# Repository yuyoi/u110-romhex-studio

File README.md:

# U110 RomHex Studio  (WIP)

<p align="center"></p>

Make your own **PCM sample cards for the Roland U-110** (and the other machines that read SN-U110 cards:
U-20, U-220, D-70, CM-32P, CM-64, MV-30, Rhodes 660/760). This is a free, open replacement for the custom-card
tools that never shipped.

> **Made by JunkSmithWizard (JSW) together with Claude (Anthropic's AI).** Claude wrote the code and did the format analysis
> (descrambling, sample coding, tables). JSW built the hardware, burned and tested every card on a real U-110,
> tested cards on a D-70 and a Rhodes 660, and made the debugging calls that cracked it: the known-good D-70 ROM control, the CD4069 noise fix, and
> pointing the D-70 debugging at its card check, which turned up the `SN-U110-` name rule.
> Reverse-engineered and shipped in one day.

Drop in WAV files, set root notes, key ranges and loops, press **Build**. You get a 512 KB image to burn on a
flash chip (e.g. SST39SF040) sitting in a card-slot adapter. Tested on a real U-110: custom multisampled,
looping and one-shot tones play correctly. Also tested on a real D-70 and a real Rhodes 660.

> **D-70 users:** the D-70 only accepts a card whose name starts with `SN-U110-`. The app always writes that
> prefix, so you pick the last 8 characters. Cards built with older versions of the app (any name) work on the
> U-110 but are not seen by the D-70. Rebuild them.

## Demo

**[Listen: u110_demo.mp3](docs/demo/u110_demo.mp3)** (1:42, recorded from a real U-110 playing a custom card)

> **⚠ AUDIO WARNING: turn your volume down first.** This demo has loud, harsh, glitchy digital sounds.

- **0:00: three samples:** custom multisampled tones from a card built with this tool.
- **Then: wavetable:** single-cycle waves and scan-morph tones (Tone → Wavetable). The stepped scan plus the
  U-110's 8-bit delta coding gives a tunable, glitchy "pleasant malfunction" sound.

## Burn cards with an ESP32

Don't have a chip programmer? An **ESP32-S3** can write the card chip itself, over USB or from a web page, for a
few dollars in parts: **[esp32-maskrom-programmer](https://github.com/yuyoi/esp32-maskrom-programmer)** (a working prototype). It wrote
a full 512 KB card image with 0 wrong bytes, no level shifters or resistors on the breadboard.

In the app: **File → Build and Burn to Programmer** (Ctrl+Shift+B) builds the card and sends it straight to the
programmer over USB; **File → Send .bin to Programmer...** sends any 512 KB image. Take the chip out of the synth first, and unplug it from the programmer before you put it back in the synth.

**Built a card, or the ESP32 programmer?** It has only been tested on one bench so far. Please
[open an issue](https://github.com/yuyoi/u110-romhex-studio/issues) and tell us what worked and what didn't
(which synth, which chip, a photo of your setup).

## Screenshots

*Styled after the U-110's front panel: backlit LCD, memory LEDs, a waveform editor with start/loop/end markers,
and colour-coded key zones on the keyboard. Click a key to hear it exactly as the U-110 will play it.*

*The card-slot adapter used for testing: slot header to SST39SF040, with a CD4069 inverting the active-high card
select. Slot pin 34 (SENS, card detect) is tied high to +5 V.*

*Optional (bottom right in the schematic): if you still hear occasional clicks or glitches, a small capacitor on
the inverter helped on the author's adapter (22 pF from CD4069 pin 2, the output of the gate that inverts the card
select, to GND). Your adapter may differ. Details and untested ideas (value, placement, two caps, type) are in
[docs/HARDWARE.md](docs/HARDWARE.md#glitches-decouple-the-logic).*

> **Warning:** if you program the chip with the ESP32 programmer, **disconnect the chip from the programmer (unplug it from the breadboard / ESP wiring) before you put it in the card slot.** An ESP left wired to the address and data lines loads and clamps the synth's 5 V bus, adds noise, and can back-power the board. Simplest: **lift the ESP off the breadboard so it has no connection at all.** Burn with the chip out of the synth; play with it out of the programmer.

## Quick start (Windows)

1. Download **`U110RomHexStudio.exe`** from the [latest release](https://github.com/yuyoi/u110-romhex-studio/releases/latest)
   and run it (check it against `SHA256SUMS.txt` if you like). No install is needed. The exe is unsigned, so Windows may show "Windows
   protected your PC": click **More info > Run anyway**. It takes a few seconds to start.
   Or, from source: install Python 3.10+, run `pip install -r src/requirements.txt`, then `run_from_source.bat`.
2. **File > Open Project** and pick `examples/demo.u110proj` to see a finished card, or start fresh:
   - **+ Tone**, then **Add WAVs**. Several files at once become either one multisampled tone (key zones) or
     one tone per file (drums, FX).
   - Root notes are read from file names (`Piano_C3.wav`, `F#2`, `60`) or from the WAV's own sampler chunk.
     Loop points saved in the WAV (Wavosaur, Audacity, Awave, ...) are used.
   - Waveform: drag **S** (start), **L** (loop start), **E** (end). Wheel zooms, Shift+wheel pans.
     **Auto loop** finds a loop and crossfades it.
   - Click the on-screen keyboard to hear a key **exactly as the U-110 will play it**: the real 8-bit
     encoding, playback rate and loop behaviour.
3. **Build Card...** writes `NAME_BURN.bin` plus a report. Burn it as-is (no byte swap).
4. On the U-110, go to EDIT > PATCH > PART > BAS and change the tone group from `I` to the slot holding the
   card. Insert and remove cards with the power off.

## Character modes (per tone)

| Mode | Sound | Memory |
|---|---|---|
| **STUDIO** | clean, filtered resample | 100% |
| **CRYSTAL** | look-ahead encoder, slightly cleaner, slower build | 100% |
| **DUSTBOX** | SP-style lo-fi: ~26 kHz, no anti-alias filter, drive | ~88% |
| **8-BIT** | early 8-bit sampler: 256 steps, 22-16 kHz, no filter | ~70% |
| **CHIPTUNE** | retro game: 6-4 bit, 16-8 kHz, sample & hold | ~50% or less |

**Amount** sets drive, rate or crush. Playback is always 12-bit, because that's what the U-110's sound chip outputs.

## Limits (set by the card format)

| | |
|---|---|
| Card size | 512 KB, about 496 KB for audio (~15 s at the native 32 kHz) |
| Card name | `SN-U110-` + 8 characters of your choice (the D-70 needs the prefix) |
| Tones | 128 per card |
| Key zones | 12 per tone |
| One sample | max 64 KB: 2 s at 32 kHz. Longer samples are automatically stored at a lower rate and stay in tune |
| Resolution | 12-bit, stored as 8-bit companded DPCM (Roland's "RS-PCM") |

When a card is too full, **Sample rate: Auto** lowers the whole card in semitone steps until it fits.
The memory bar shows how much is used.

## Also in the box

- **File > Import card .bin**: open any SN-U110 card image (a Roland dump or one of your own) to edit it,
  and extract its samples as WAVs.
- **File > Import sampler CD (Akai / Roland S-7xx)**: browse an Akai S1000/S1100 or Roland S-760/S-770 sampler CD (`.iso`,
  `.img`, `.tao`, `.nrg` of the raw disc), pick programs or patches, and they become tones: key ranges, root notes, tuning and loops are kept, stereo L/R pairs
  are mixed to mono, and the samples are trimmed to fit the card (your own tones are never touched). See `docs/AKAI.md`
  and `docs/ROLAND.md`.
- `src/u110card.py` on the command line: `info`, `wavs` (extract samples) and `convert` (MAME card dump to
  burnable connector order).
- `docs/FORMAT.md`: the reverse-engineered card format.
- `docs/HARDWARE.md` + `docs/adapter_schematic.png`: card-slot pinout, adapter wiring and the byte-order pitfall.

## Important: byte order

Images from MAME's `sn-u110-xx.bin` set have address lines **A8..A15 reversed** compared with the card slot.
Burned as-is on a straight-wired adapter, they load with garbled names and no sound. This app always writes
**connector order**, the right order for a straight adapter. `u110card.py convert` fixes MAME dumps.

## Status: work in progress 🚧

This is an early release. It works, and it's tested on a real U-110, but expect rough edges and changes.

**Planned:**
- **A reprogrammable card:** an RP2040 (or similar) on a custom PCB, either as a card or fitted inside the
  unit, so you can load new sounds over USB without pulling and burning chips.
- Dual-layer, velocity-switch and drum-kit tone types.
- Confirmed support on the U-20 and U-220.

Ideas, bug reports and test results are very welcome. Open an issue.

## Legal

Not affiliated with or endorsed by Roland Corporation. "Roland", "U-110" and "SN-U110" are trademarks of
Roland Corporation. This package contains **no Roland data**: the demo sounds were synthesized for it. Only
share cards containing sounds you have the rights to. Format knowledge builds on MAME's open-source Roland
drivers (BSD-3-Clause) and the U-110 service notes.

License: MIT (see `LICENSE`).

---

**Thanks for enjoying, and God bless you!** — JSW

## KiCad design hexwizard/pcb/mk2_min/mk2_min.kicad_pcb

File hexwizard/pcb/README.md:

# Hex Wizard MK2 card (KiCad 10): proposed prototype, UNTESTED

**Status: proposed prototype. Nothing here has been fabricated, assembled or tested.** The footprints, power switching and firmware are unverified (the finger order follows a working clone card and the long GND finger is confirmed). Check against a real U-110 card before ordering boards.

A Roland U-110 / SN-U110 ROM card that carries its own **SST39SF040 flash** and an **ESP32-S3** (WiFi/USB), so the card can be re-burned without a programmer.

| Board | What it is | State |
|---|---|---|
| [`mk2_min/`](mk2_min) | The minimum-parts card: 23 parts, SST39SF040 (TSOP-32) + ESP32-S3-WROOM-1-N16, USB-C. | Schematic + fully routed 2-layer PCB (GND pour), KiCad DRC: 0 unconnected, no clearance errors |
| [`mk2_vero/`](mk2_vero) | No components: all 34 fingers traced to labeled 2.54 mm holes at the back of the card plus a blank perf field. Single sided, made for a hobby mill. | PCB only, DRC clean apart from the expected finger edge-clearance |

Previews: [`img/`](img). BOM: [`mk2_min/BOM.csv`](mk2_min/BOM.csv).

## mk2_min: how it works
- ESP GPIOs go **straight to the SST bus** (A0..A18, D0..D7, WE#). No buffers or series resistors, to keep the part count minimal.
- The slot's CS is **active HIGH**; one 2N7002 (Q1) inverts it into the SST's CE#.
- Pull-ups on CS, /OE and WE# mean a card that is out of the synth has CE# low, OE# high and WE# high, which is what a burn needs.
- Two Schottky diodes OR the slot 5 V and USB 5 V into the 5 V rail; an AP2112K makes 3.3 V.
- Q2 (N-FET in the ESP ground leg, gate on the 5 V rail) switches the ESP on by itself when the card is inserted or USB is plugged in.
- USB-C is the ESP's native USB. BOOT/user button on IO0, 4-pin header for a 0.96 in I2C OLED.

### Parts (BOM)
| Qty | Refs | Part |
|---|---|---|
| 1 | U1 | SST39SF040-70-4C-TU, 512 KB flash, 8 x 14 mm TSOP-32 |
| 1 | U2 | ESP32-S3-WROOM-1-N16 (not an octal-PSRAM R8 part) |
| 1 | U3 | AP2112K-3.3 LDO |
| 2 | Q1, Q2 | 2N7002 (SOT-23); Q2 may need an AO3400 if the ESP browns out |
| 2 | D1, D2 | SS14W Schottky (SOD-123) |
| 1 | J4 | USB-C 16-pin receptacle (HRO TYPE-C-31-M-12 footprint) |
| 1 | SW1 | SMD tact switch (KMR2 style) |
| 1 | J2 | 1x4 pin header (OLED) |
| 2 | C2, C3 | 10 uF 0805 |
| 3 | C1, C4, C5 | 100 nF x2, 1 uF x1 (0603) |
| 8 | R1-R7 | 10 k x2, 100 k x3, 5.1 k x2 (0603) |
| 1 | J1 | card-edge fingers (on the PCB) |

### GPIO map (the firmware has NOT been ported to this)
A0..A18 = 18, 8, 9, 10, 11, 12, 13, 14, 21, 35, 36, 37, 38, 39, 40, 41, 42, 47, 48; D0..D7 = 1, 2, 4, 5, 6, 7, 15, 16; WE# = 17; OLED SDA/SCL = 3/46; BOOT/user button = 0; USB D-/D+ = 19/20. IO45 is left alone (high at boot can select 1.8 V flash).

## Known caveats and risks
- **Finger order** comes from the working clone card's Gerber (all 34 fingers on the bottom copper, long GND finger = pin 32, third from one end, then pin 33 open and pin 34 SENS; pin 1 at the far end, on the right seen from the top with the card edge down) and the long finger being GND is confirmed on a real card. Card pins 21 and 33 are left open (function unknown); pin 34 SENS is tied to +5 V on the original. Still worth a continuity check on a real card before ordering.
- **The synth's 5 V reaches the ESP pins** whenever the card is in the synth, and the ESP now powers up there too (Q2 closes on the slot 5 V). That can damage the ESP; there is no isolation by design.
- Q2 is a 2N7002 (about 2-3 ohm on-resistance); swap for an AO3400 if WiFi bursts brown the ESP out.
- The card outline (53 x 99.5 mm) was measured from a clone card, not a Roland spec; slot height limits and card thickness are unknown, and the fingers need a bevelled edge and a hard-gold or ENIG finish.
- The TSOP footprint is the 8 x 14 mm package; change `SST_FP` in `gen/mk2_min_gen.py` for the 8 x 20 mm one.
- Fine-pitch TSOP and 96 vias make `mk2_min` a fab job, not a mill job.
- The card-edge footprint ([`SN-U110_CardEdge.pretty`](SN-U110_CardEdge.pretty)) is an original drawing from measured contact positions (pitch, width, length); no third-party artwork or routing is included.

## Regenerating
`gen/mk2_min_gen.py` / `gen/mk2_vero_gen.py` rebuild the projects (KiCad 10 must be installed for its libraries). Regenerating `mk2_min` produces the **unrouted** board; `gen/fr_scratch.py` plus a Freerouting 2.4 jar and Java 25 reproduce the autoroute (GND routed as copper, then a solid GND pour). `gen/verify.py mk2_min` checks schematic and PCB nets agree.

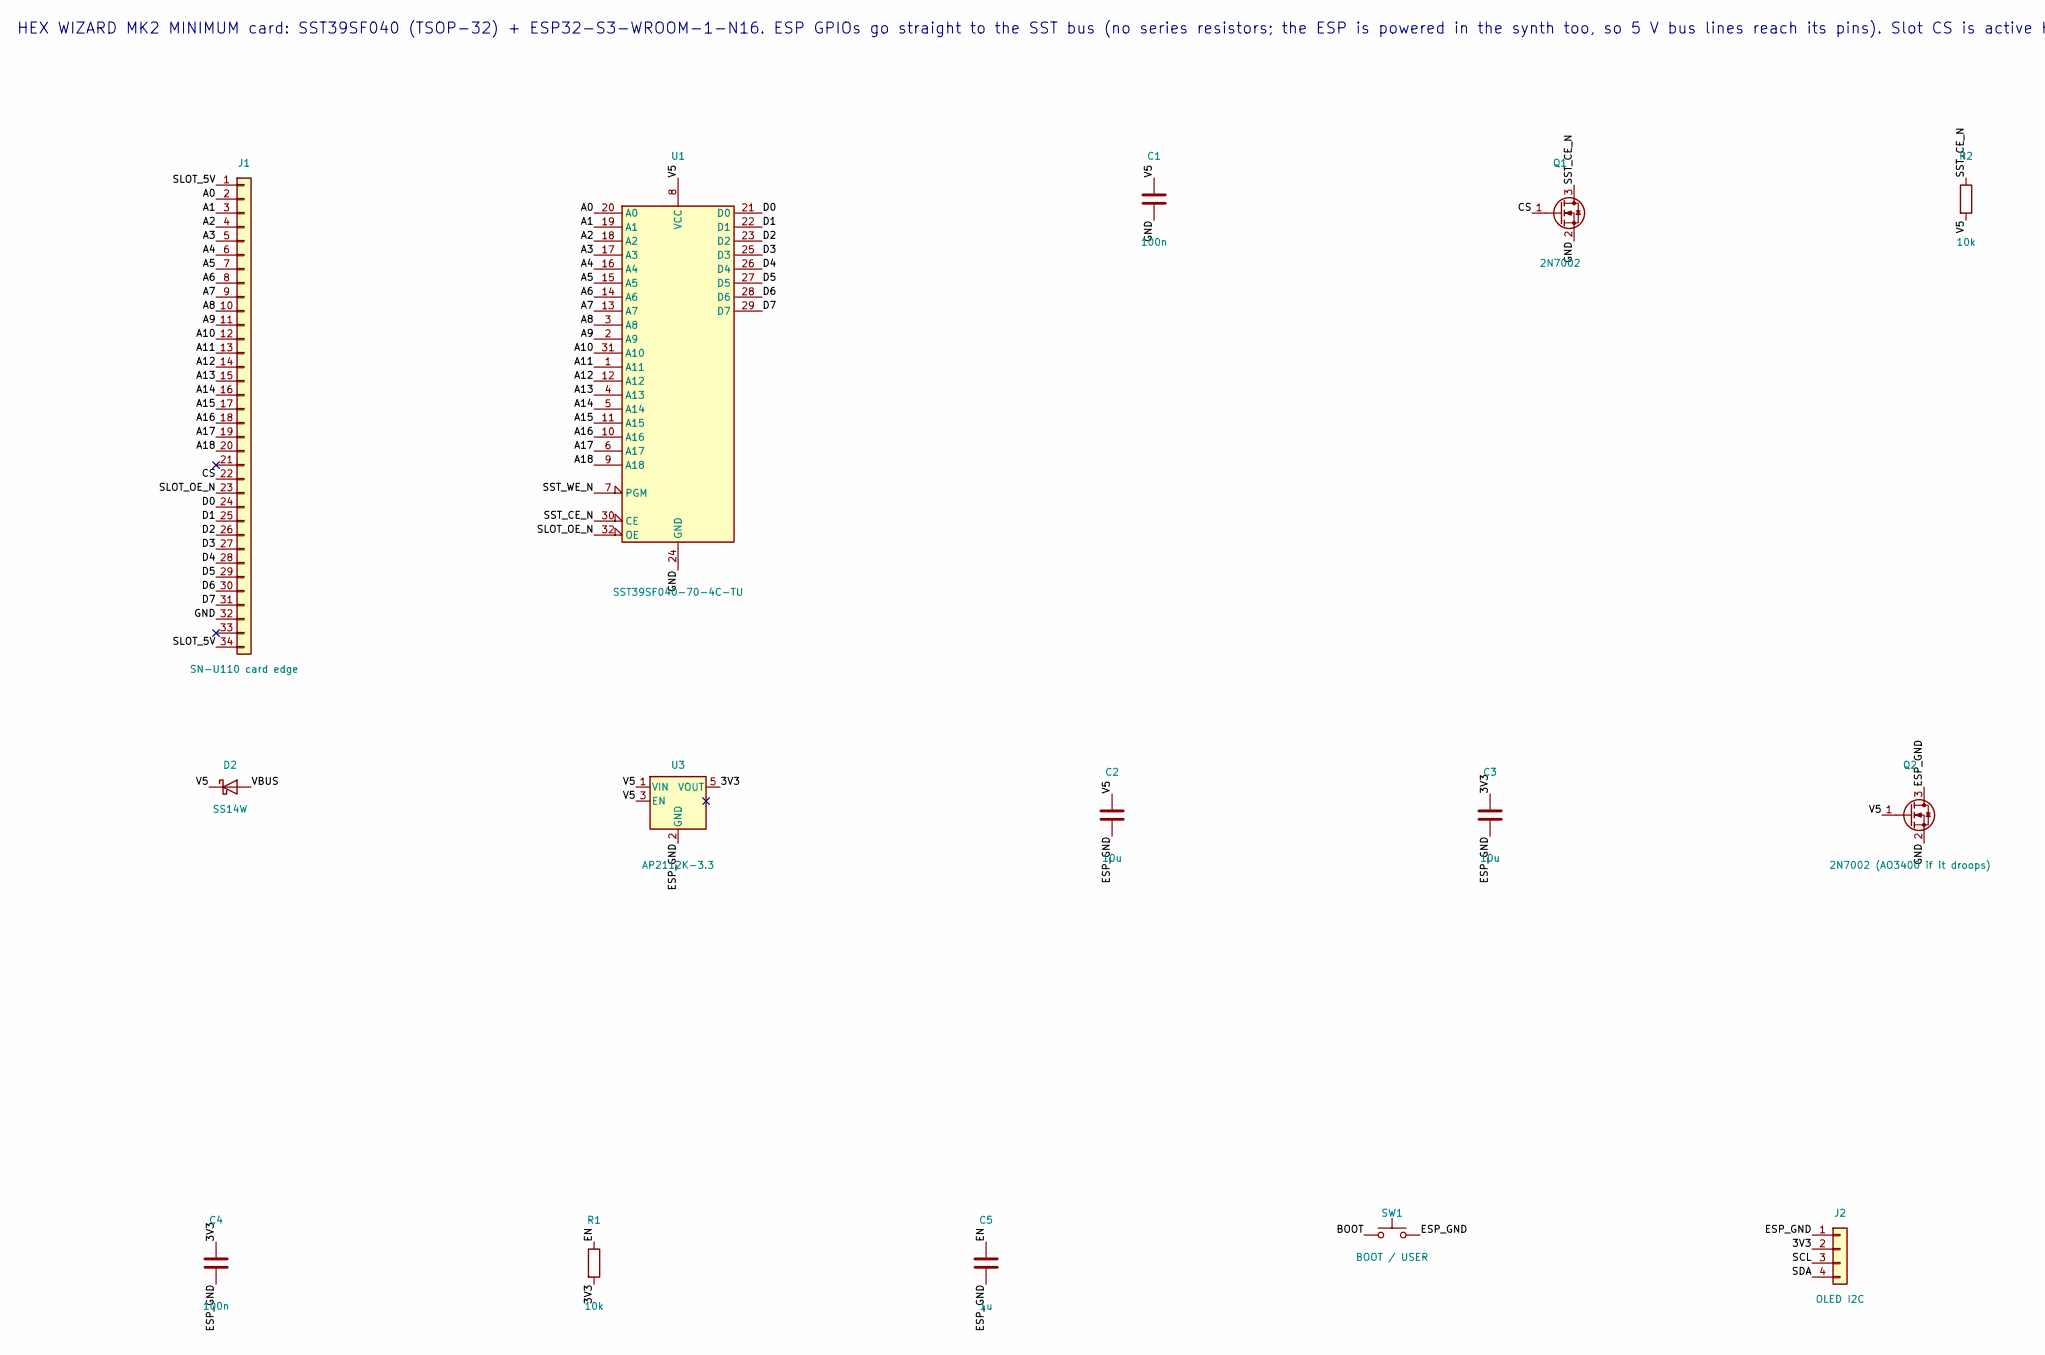
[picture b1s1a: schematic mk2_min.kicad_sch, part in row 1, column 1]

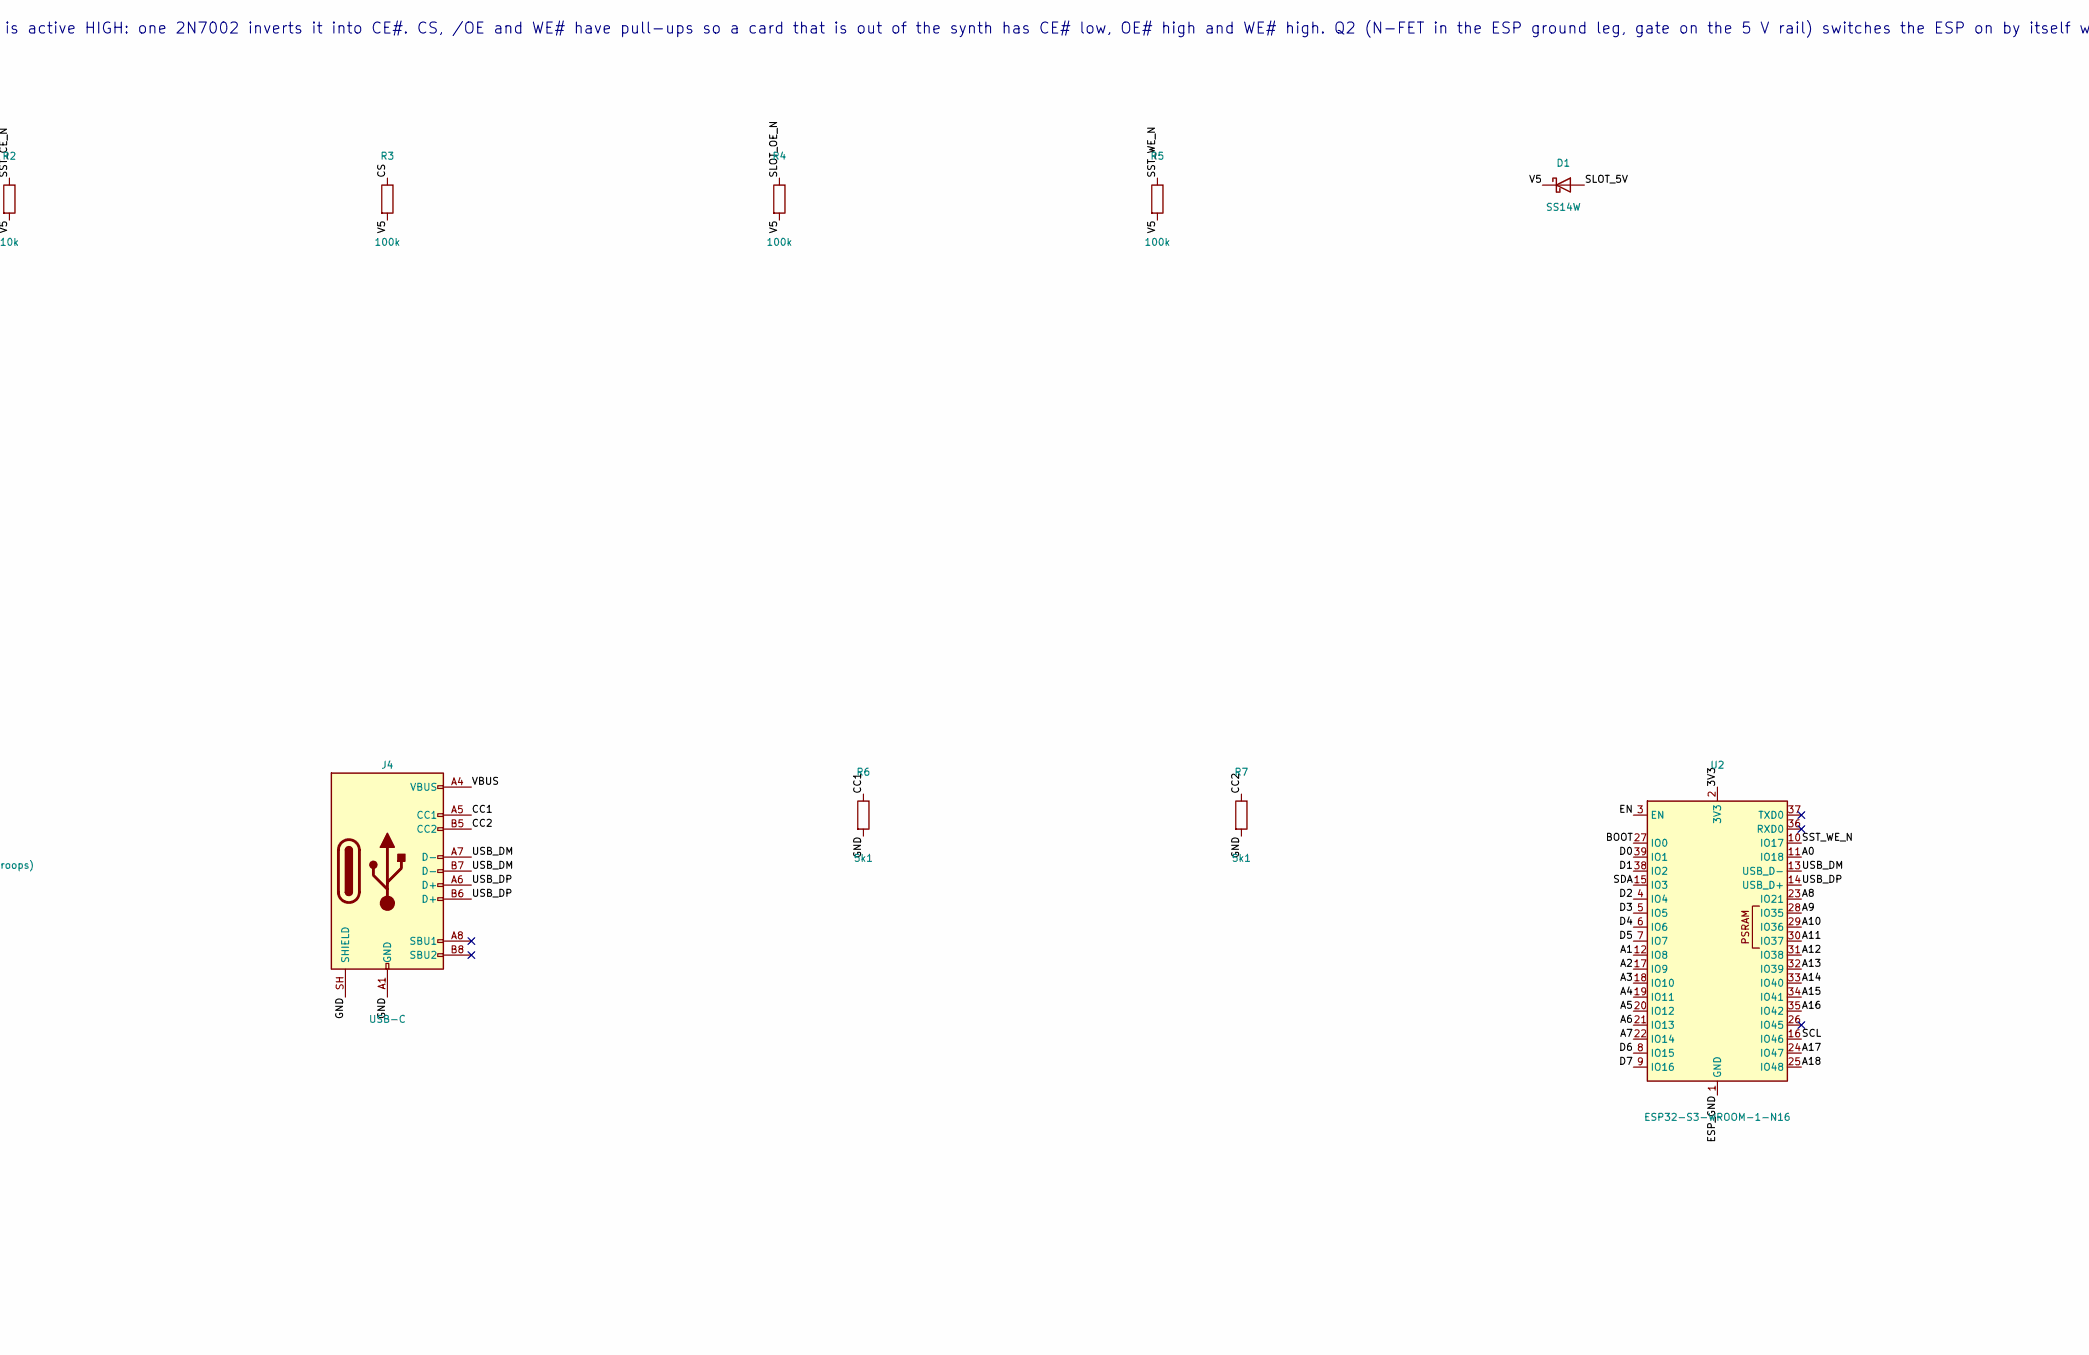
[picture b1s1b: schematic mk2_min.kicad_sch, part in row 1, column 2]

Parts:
C1, C4: 100n; C_0603_1608Metric
C2, C3: 10u; C_0805_2012Metric
C5: 1u; C_0603_1608Metric
D1, D2: SS14W; D_SOD-123
J1: SN-U110 card edge; SN-U110_CardEdge
J2: OLED I2C; PinHeader_1x04_P2.54mm_Vertical
J4: USB-C; USB_C_Receptacle_HRO_TYPE-C-31-M-12
Q1: 2N7002; SOT-23
Q2: 2N7002 (AO3400 if it droops); SOT-23
R1, R2: 10k; R_0603_1608Metric
R3, R4, R5: 100k; R_0603_1608Metric
R6, R7: 5k1; R_0603_1608Metric
SW1: BOOT / USER; SW_Push_1P1T_NO_CK_KMR2
U1: SST39SF040-70-4C-TU; TSOP-I-32_12.4x8mm_P0.5mm
U2: ESP32-S3-WROOM-1-N16; ESP32-S3-WROOM-1
U3: AP2112K-3.3; SOT-23-5

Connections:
3V3: C3.1, C4.1, J2.2, R1.2, U2.2 (3V3), U3.5 (VOUT)
A0: J1.2, U1.20 (A0), U2.11 (IO18)
A1: J1.3, U1.19 (A1), U2.12 (IO8)
A2: J1.4, U1.18 (A2), U2.17 (IO9)
A3: J1.5, U1.17 (A3), U2.18 (IO10)
A4: J1.6, U1.16 (A4), U2.19 (IO11)
A5: J1.7, U1.15 (A5), U2.20 (IO12)
A6: J1.8, U1.14 (A6), U2.21 (IO13)
A7: J1.9, U1.13 (A7), U2.22 (IO14)
A8: J1.10, U1.3 (A8), U2.23 (IO21)
A9: J1.11, U1.2 (A9), U2.28 (IO35)
A10: J1.12, U1.31 (A10), U2.29 (IO36)
A11: J1.13, U1.1 (A11), U2.30 (IO37)
A12: J1.14, U1.12 (A12), U2.31 (IO38)
A13: J1.15, U1.4 (A13), U2.32 (IO39)
A14: J1.16, U1.5 (A14), U2.33 (IO40)
A15: J1.17, U1.11 (A15), U2.34 (IO41)
A16: J1.18, U1.10 (A16), U2.35 (IO42)
A17: J1.19, U1.6 (A17), U2.24 (IO47)
A18: J1.20, U1.9 (A18), U2.25 (IO48)
BOOT: SW1.1, U2.27 (IO0)
CC1: J4.A5 (CC1), R6.1
CC2: J4.B5 (CC2), R7.1
CS: J1.22, Q1.1 (G), R3.1
D0: J1.24, U1.21 (D0), U2.39 (IO1)
D1: J1.25, U1.22 (D1), U2.38 (IO2)
D2: J1.26, U1.23 (D2), U2.4 (IO4)
D3: J1.27, U1.25 (D3), U2.5 (IO5)
D4: J1.28, U1.26 (D4), U2.6 (IO6)
D5: J1.29, U1.27 (D5), U2.7 (IO7)
D6: J1.30, U1.28 (D6), U2.8 (IO15)
D7: J1.31, U1.29 (D7), U2.9 (IO16)
EN: C5.1, R1.1, U2.3 (EN)
ESP_GND: C2.2, C3.2, C4.2, C5.2, J2.1, Q2.3 (D), SW1.2, U2.1 (GND), U2.40 (GND), U2.41 (GND), U3.2 (GND)
GND: C1.2, J1.32, J4.A1 (GND), J4.A12 (GND), J4.B1 (GND), J4.B12 (GND), J4.SH (SHIELD), Q1.2 (S), Q2.2 (S), R6.2, R7.2, U1.24 (GND)
SCL: J2.3, U2.16 (IO46)
SDA: J2.4, U2.15 (IO3)
SLOT_5V: D1.2 (A), J1.1, J1.34
SLOT_OE_N: J1.23, R4.1, U1.32 (OE)
SST_CE_N: Q1.3 (D), R2.1, U1.30 (CE)
SST_WE_N: R5.1, U1.7 (PGM), U2.10 (IO17)
USB_DM: J4.A7 (D-), J4.B7 (D-), U2.13 (USB_D-)
USB_DP: J4.A6 (D+), J4.B6 (D+), U2.14 (USB_D+)
V5: C1.1, C2.1, D1.1 (K), D2.1 (K), Q2.1 (G), R2.2, R3.2, R4.2, R5.2, U1.8 (VCC), U3.1 (VIN), U3.3 (EN)
VBUS: D2.2 (A), J4.A4 (VBUS), J4.A9 (VBUS), J4.B4 (VBUS), J4.B9 (VBUS)

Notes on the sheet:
HEX WIZARD MK2 MINIMUM card: SST39SF040 (TSOP-32) + ESP32-S3-WROOM-1-N16. ESP GPIOs go straight to the SST bus (no series resistors; the ESP is powered in the synth too, so 5 V bus lines reach its pins). Slot CS is active HIGH: one 2N7002 inverts it into CE#. CS, /OE and WE# have pull-ups so a card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

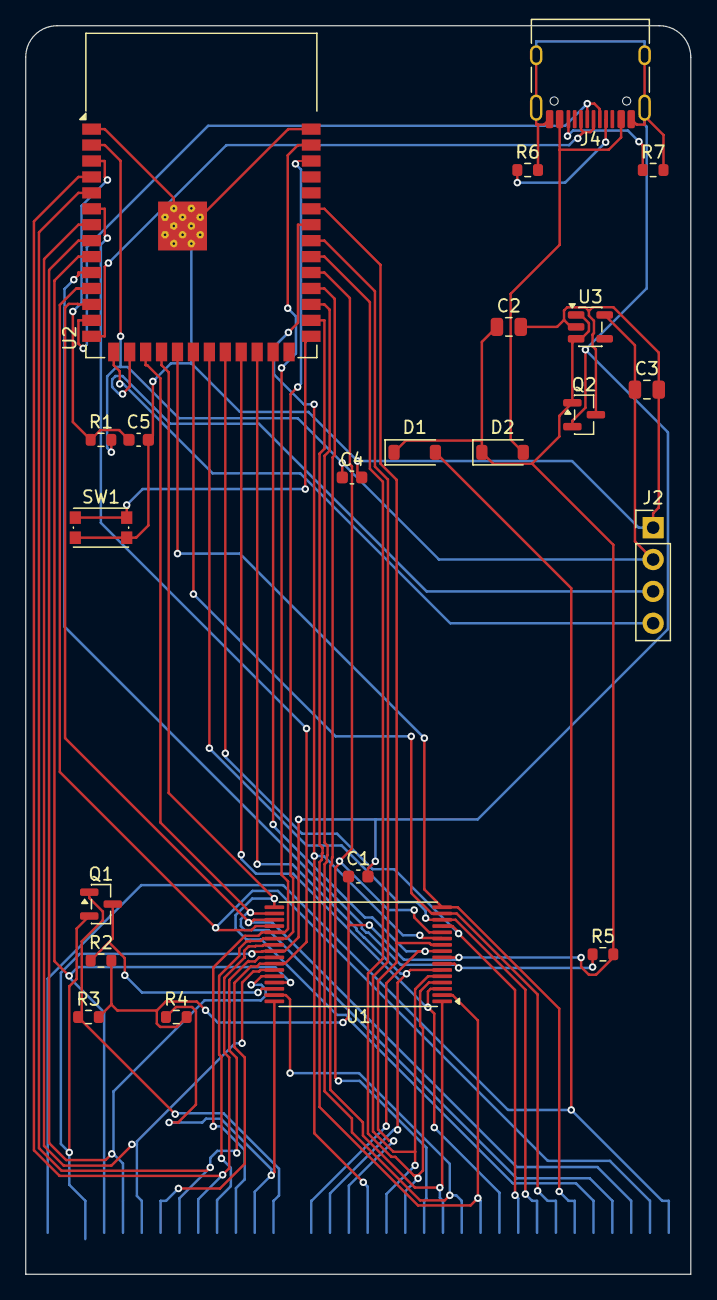
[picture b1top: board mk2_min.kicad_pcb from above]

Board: 2 copper layers, 53.0 x 99.5 mm, 23 parts (1 on the bottom side), 45 nets.

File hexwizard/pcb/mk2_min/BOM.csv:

Qty,Refs,Value,Footprint,Suggested part / note
1,J1,SN-U110 card edge,SN-U110_CardEdge:SN-U110_CardEdge,Board edge fingers (no part)
1,U1,SST39SF040-70-4C-TU,Package_SO:TSOP-I-32_12.4x8mm_P0.5mm,SST39SF040-70-4C-TU (8x14 mm TSOP-32); the 8x20 mm package needs the 18.4x8 footprint
1,U2,ESP32-S3-WROOM-1-N16,RF_Module:ESP32-S3-WROOM-1,Espressif ESP32-S3-WROOM-1-N16 (no octal PSRAM: IO35-37 are address lines)
1,U3,AP2112K-3.3,Package_TO_SOT_SMD:SOT-23-5,AP2112K-3.3 LDO (600 mA)
1,Q1,2N7002,Package_TO_SOT_SMD:SOT-23,2N7002 CS inverter (slot CS is active HIGH)
1,Q2,2N7002 (AO3400 if it droops),Package_TO_SOT_SMD:SOT-23,ESP ground switch; use AO3400 if the ESP browns out
2,D1 D2,SS14W,Diode_SMD:D_SOD-123,Schottky 1 A (SS14W / B5819W) 5 V OR-ing
1,J4,USB-C,Connector_USB:USB_C_Receptacle_HRO_TYPE-C-31-M-12,USB-C 16-pin receptacle (HRO TYPE-C-31-M-12 or equivalent)
1,SW1,BOOT / USER,Button_Switch_SMD:SW_Push_1P1T_NO_CK_KMR2,SMD tact switch (C&K KMR2 style)
1,J2,OLED I2C,Connector_PinHeader_2.54mm:PinHeader_1x04_P2.54mm_Vertical,1x4 header for a 0.96 in I2C OLED: GND 3V3 SCL SDA
2,C2 C3,10u,Capacitor_SMD:C_0805_2012Metric,10 uF 0805
2,C1 C4,100n,Capacitor_SMD:C_0603_1608Metric,100 nF 0603
1,C5,1u,Capacitor_SMD:C_0603_1608Metric,1 uF 0603 (EN)
2,R1 R2,10k,Resistor_SMD:R_0603_1608Metric,10 k 0603 (EN pull-up; CE# pull-up)
3,R3 R4 R5,100k,Resistor_SMD:R_0603_1608Metric,100 k 0603 (CS, /OE, WE# pull-ups)
2,R6 R7,5k1,Resistor_SMD:R_0603_1608Metric,5.1 k 0603 (USB-C CC)

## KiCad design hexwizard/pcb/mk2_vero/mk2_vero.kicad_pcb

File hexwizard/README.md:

# U110 HexWizard

The U-110 flavour of the [ESP32 maskrom programmer](https://github.com/yuyoi/esp32-maskrom-programmer).
Same hardware and burn firmware, plus a 128x64 OLED that plays a boot animation and then idles as a small
creature while the programmer is ready. **Working prototype**: the programmer and the OLED animation run on the
author's bench; the three-button ladder below is designed and calculated but not yet tested on real hardware.

The general programmer repo stays plain (status screen only). Everything here is specific to this project.

## What it does

- **Boot:** "U110" types in, "HEX WIZARD" types under it, the picture dissolves in, zooms to her face, and the
  logo block settles beside her head (about 6 s, once).
- **Idle:** she blinks about every 3 seconds and a thin glitch band runs across the lower half now and then.
- **Status screen:** IP address, stored cards with their tone names, free flash, burn progress. It takes over
  during a burn and when a burn finishes or fails, and falls back to the creature after 20 s.
- **Buttons:** short press on the single button, or UP / DOWN / SELECT on the ladder (see below).

> **Warning:** never leave the ESP wired to the chip while it is in a synth. See the warning in the
> [programmer README](https://github.com/yuyoi/esp32-maskrom-programmer#readme).

## Display settings (web page, Display tab)

Join the WiFi network `SST-PROG` (password `u110cards`), open the programmer's page (`http://192.168.4.1/`, or `http://sstprog.local/` once you have added your home WiFi on the Cards tab) and pick the **Display** tab:

- **Glitch band** on or off.
- **Show the IP** at the bottom left of the creature screen (small 4x6 text, it cuts into the picture a little).
- **Idle animation:** *Look around*, *Gasp*, *Look at the rack*, *Random* (picks one every few seconds), or *Off* (blink only). **Play it now** previews the chosen one.
- **Storage:** flash used and total, percent filled, card count and free space. The OLED status screen shows the same in its bottom line, for example `2 cards 10%/9.8M`.

- **Screen tab:** a live mirror of the OLED (about 3 frames a second) with **Up / Down / Select** buttons that work like the real ones, so you can browse the stored cards and switch between the creature and the status screen from a browser. It pauses while a burn runs, because the WiFi radio is off then.

Settings are saved on the device. From a terminal the same thing is `UI gl=0 ip=1 an=2 play=1` over the serial port (921600 baud), and plain `UI` prints the current state.

### Settings menu on the device

The same settings are on the OLED. With the **single button** a short press moves on and a **hold (0.7 s)** selects:
creature -> (press) status screen -> (hold) **Settings**. With the **three-button ladder**, Select on the status screen
opens Settings, Up/Down move and Select changes the item. Items: *Glitch band* on/off, *Show IP* on/off,
*Animation* (Look around, Gasp, Rack, Random, Off), *Play it now*, *Back*. Changes are saved at once and match the web
page. The menu closes after 20 s without a press.

## Wiring (on top of the programmer's pin map)

| OLED (0.96" SSD1306, I2C) | ESP32-S3 |
|---|---|
| VCC | 3V3 |
| GND | GND |
| SDA | GPIO4 |
| SCL | GPIO5 |

GPIO6 is the button input. Nothing else on the DevKitC-1 (N16R8) is free: the bus uses the rest, GPIO35 to 37
belong to the PSRAM, and 43/44 are the USB-UART lines.

### Buttons

**Single button:** GPIO6 to GND. A press goes from the creature to the status screen, then steps through the stored
cards, then back to the creature.

**Three buttons on one pin (resistor ladder, all E12 values):**

```
3V3 --[6.8k]--+-----------+----> GPIO6 (ADC)
              |           |
           [18k]        [100nF]
              |           |
             GND         GND

node --[1.5k]-- UP ------- GND
node --[4.7k]-- DOWN ----- GND
node --[15k]--  SELECT --- GND
```

| State | Voltage |
|---|---|
| idle | 2.40 V |
| SELECT | 1.80 V |
| DOWN | 1.17 V |
| UP | 0.56 V |

The values come from `oled_anim/ladder_opt.py`, which searches E12 resistors for the widest gaps (0.56 V) and
checks 1 % tolerances (worst case 0.54 V). The firmware detects at boot whether a ladder is fitted (the
serial log prints "GPIO6 reads ... mV" and which mode it chose) and otherwise treats GPIO6 as a plain button.
UP and DOWN step through the stored cards and repeat while held. SELECT switches between the creature and
the status screen.

## Build and flash

Same as the programmer: Arduino CLI with the `esp32:esp32` core and the U8g2 library, through the board's
**UART** USB-C port.

```bash
arduino-cli compile --fqbn "esp32:esp32:esp32s3:FlashSize=16M,PartitionScheme=app3M_fat9M_16MB" firmware/sst_programmer
arduino-cli upload -p COMx --fqbn "esp32:esp32:esp32s3:FlashSize=16M,PartitionScheme=app3M_fat9M_16MB" firmware/sst_programmer
```

Flashing the app does not touch the stored cards.

The OLED runs on I2C at 1 MHz with the panel oscillator at its maximum, which keeps camera shots of the screen free of tearing. If your display shows garbled pixels, drop `setBusClock` and `Wire.setClock` back to 400000.

## Changing the animation

`oled_anim/anim3.py` turns the drawings in `art/` into the firmware frames (`firmware/sst_programmer/splash.h`,
62 unique 128x64 frames, about 60 KB) and a preview GIF. It needs Python with Pillow and NumPy.

```bash
cd oled_anim
python anim3.py
```

- `art/girl_redraw2.png`: black ink on white, 1280 x 600. `art/girl_closed.png`: the same drawing with the eyes closed, used for the blink.
- Far view uses a sharpened, dithered downscale; the zoom dissolves into a cleaner contrast-stretched one. At 128x64,
  bold single strokes survive and hairlines and dense hatching do not.
- Text uses a hand-made 5x7 pixel font defined in the script.
- The idle animations (look left and right, look at the rack, gasp) are built from the drawing by redrawing the eyes and mouth. To use your own drawings instead, save full frames at 1280 x 600 as `art/girl_look_left.png`, `art/girl_look_right.png`, `art/girl_look_rack.png`, `art/girl_gasp1.png` and `art/girl_gasp2.png`, then run the script; it uses any of those that exist.

## Burning tips (what went wrong on the bench)

- **Check the contacts first.** A chip erase draws more current than programming. A loose or high-resistance joint on VDD (pin 32) or GND (pin 16) can make the erase quietly fail while every byte still programs, leaving the old data ANDed with the new. Use the best contacts you have for the power pins, put 100 nF plus 10 uF across pins 32 and 16, and re-seat cheap breadboard headers before each burn.
- The firmware resets the chip's command state (`F0H`) at boot and before each erase, and follows the chip erase with a per-sector erase pass (about 4 s more).
- `ERASE CHIP` and `ERASE` (sectors only) over the serial port erase without writing, so you can read the chip in your programmer and check for all `FF`.
- The page's status request times out after 4 s and keeps retrying, so it recovers when the WiFi comes back after a burn.

## Built one? Tell us

If you build any of it, please [open an issue](https://github.com/yuyoi/u110-romhex-studio/issues) with what you
built, what worked and what didn't, and a photo of the wiring if you can. Reports of failures are as useful as
reports of successes.

Drawings by JunkSmithWizard (JSW). Firmware and scripts written with Claude (Anthropic's AI).

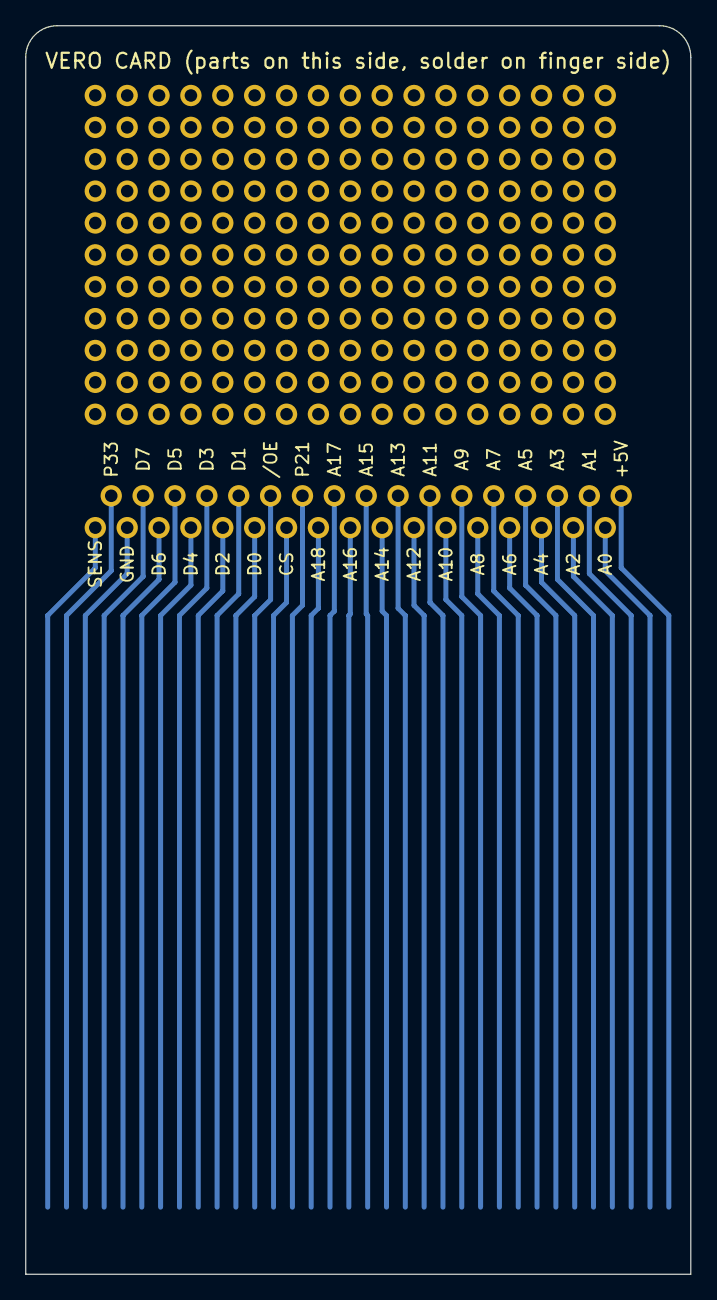
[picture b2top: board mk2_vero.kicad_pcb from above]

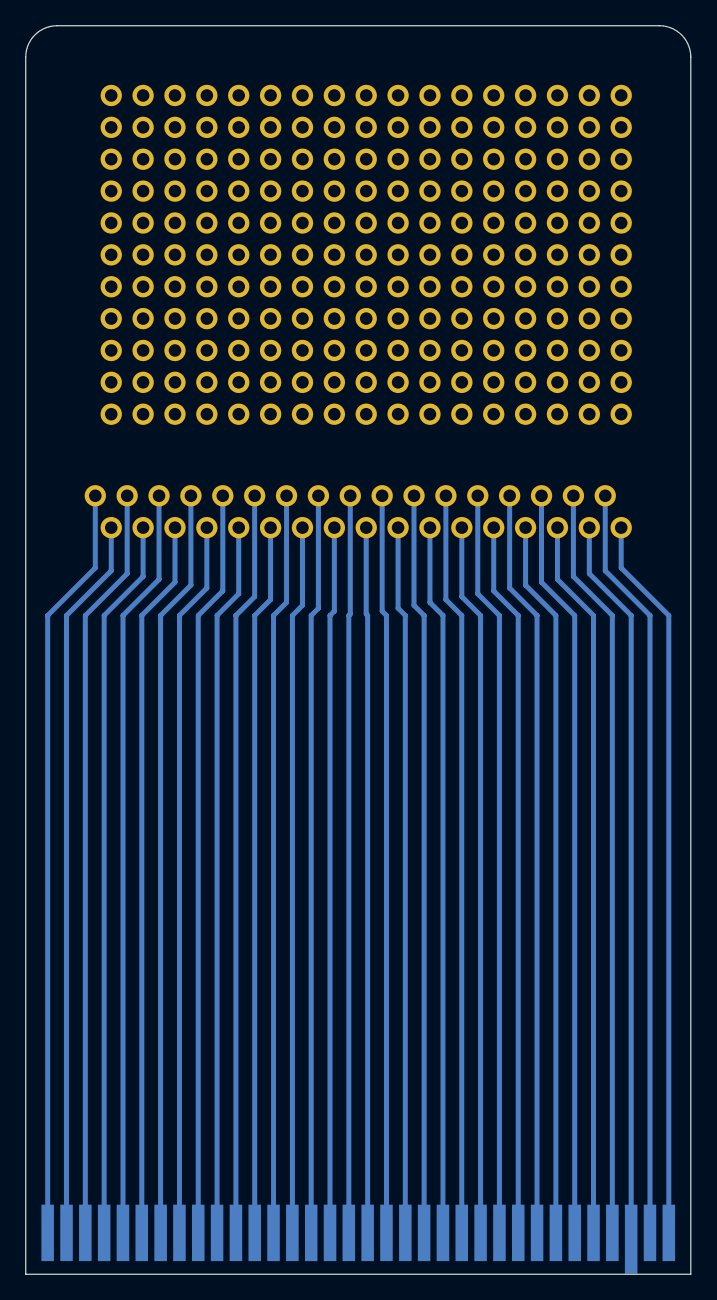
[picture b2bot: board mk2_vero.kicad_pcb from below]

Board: 2 copper layers, 53.0 x 99.5 mm, 3 parts (3 on the bottom side), 34 nets.

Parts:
J1: SN-U110 card edge; SN-U110_CardEdge
J2: breakout; Breakout_2x17
J3: perf field; PerfField

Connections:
+5V: J1.1, J2.1
/OE: J1.23, J2.23
A0: J1.2, J2.2
A1: J1.3, J2.3
A2: J1.4, J2.4
A3: J1.5, J2.5
A4: J1.6, J2.6
A5: J1.7, J2.7
A6: J1.8, J2.8
A7: J1.9, J2.9
A8: J1.10, J2.10
A9: J1.11, J2.11
A10: J1.12, J2.12
A11: J1.13, J2.13
A12: J1.14, J2.14
A13: J1.15, J2.15
A14: J1.16, J2.16
A15: J1.17, J2.17
A16: J1.18, J2.18
A17: J1.19, J2.19
A18: J1.20, J2.20
CS: J1.22, J2.22
D0: J1.24, J2.24
D1: J1.25, J2.25
D2: J1.26, J2.26
D3: J1.27, J2.27
D4: J1.28, J2.28
D5: J1.29, J2.29
D6: J1.30, J2.30
D7: J1.31, J2.31
GND: J1.32, J2.32
P21: J1.21, J2.21
P33: J1.33, J2.33
SENS: J1.34, J2.34
